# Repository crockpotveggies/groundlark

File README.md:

# Groundlark — open hardware for seismic and environmental monitoring

Groundlark is a family of hardware boards and companion software for seismic
and environmental monitoring. Each board has its own hardware directory, with
shared component libraries, interfaces and validation tools.

The family has **three products**: the Groundlark FPGA HAT, Skylark and
Burrowlark USB sensor heads. All share the sensor contracts, simulation tools and local workbench.

## Groundlark

**Seismic monitoring on a Raspberry Pi.** The active
[Groundlark FPGA HAT](hw/groundlark-fpga-hat/README.md), model **DAQHAT-01**, is a
140 × 56 mm, six-layer FR-4 board with three XYZ LSM6DSO IMUs and an ADS122C04
input for an external Racotech geophone, plus a fitted DLVR infrasound sensor and u-blox MAX-M10S GNSS with a side-facing SMA antenna connector. The stack is **Pi → HAT → Trenz
Artix-7 200T FPGA**. Pi acquisition works independently of a configured FPGA.

The [internal FPGA link](docs/fpga-host-link.md) provides six QSPI wires, UART,
reset and switched Pi-driven JTAG. An SPI echo bitstream is implemented;
accelerated sensor processing and native quad transfers remain future work.
The FPGA uses a separate Nexys Video-compatible 12 V, center-positive adapter through J83 and an onboard 3.326 V converter. See the [power limits](docs/trenz-hat.md).

**Status:** active prototype. Physical power, fit, timing, noise and thermal
qualification remain pending. See the [stack assembly guide](docs/stack-assembly.md),
[JLCPCB instructions](docs/jlcpcb-assembly.md) and [bench procedure](docs/bench-procedure.md).
The JLCPCB package targets one assembled HAT; sourcing, placement and J1 fit
checks remain open. Fabrication packages stay local in ignored `hw/releases/`.

*R3 [prototype enclosure](hw/mechanical/daqhat-01-case/README.md), current
140 mm HAT CAD with GNSS/SMA, infrasound, TI Pi supervision and independent FPGA power, vendor Trenz components and a detailed
[Pi 4B model](hw/shared/models/raspberrypi4/README.md) by integrated-circuit / FreeCAD
community (CC BY 3.0). Clear PETG appearance, risers, geophone and wiring are approximate.
Physical fit remains unqualified. [Render provenance](docs/images/groundlark-gnss.json).*

[Closed enclosure render provenance](docs/images/groundlark-gnss-closed.json).
Measured gain/offset workflows and PCB probe access are in the
[calibration guide](docs/calibration.md). Seismic recordings support local
[miniSEED export](docs/miniseed.md).

## Skylark

**Outdoor air-quality monitoring over USB.** [Skylark USB](hw/skylark-usb/README.md)
combines a vertical **90 × 100 mm PCB** with a removable sensor tray and a
**130 × 94 × 185 mm bell enclosure**.

- **Particles:** Plantower PMS5003, with separate downward-facing inlet and exhaust paths.
- **Gases:** socketed SGX-7SO2-AQ-20 sulfur dioxide and SGX-7H2S-AQ-25 hydrogen sulfide cells.
- **Weather:** SHT40 temperature/humidity and BMP390 barometric pressure.
- **Connection:** USB-C power and data through an STM32F072 microcontroller.
- **Housing:** printable bell, rear M4 keyhole mounts and a removable tray with
  separate PMS cradle and splash cover. Bottom ventilation is sheltered by a 25 mm skirt.

[Prototype firmware](sw/skylark/README.md) implements sensor acquisition and
USB streaming. The shared workbench includes Skylark simulation, recording/replay,
board-specific tests and an interactive 3D PCB. Gas data retains separate raw
working and auxiliary electrode counts; concentrations require calibration.

**Status:** Rev A PCB, Rev G enclosure and prototype firmware are implemented.
Physical fit, USB power behavior, analog performance, gas response and weather
resistance still require qualification. The ventilated enclosure has no assigned
IP rating. Follow the [PCB guide](hw/skylark-usb/README.md) and
[enclosure assembly instructions](hw/skylark-usb/mechanical/bell/README.md).

*Render: native PCB artwork and authored component models in the CAD-derived
tray, with the bell set beside it. Component bodies are dimension envelopes;
fasteners and cable dressing are illustrative. [Render provenance](docs/images/skylark-assembly.json).*

## Burrowlark

**Remote magnetic and enclosure-climate sensing over USB.**
[Burrowlark USB](hw/burrowlark-usb/README.md), model **DAQUSB-01**, carries an
RM3100 magnetometer and SHT45 temperature/humidity sensor. It connects to the Pi through USB-C for power and data.
The DLVR infrasound sensor is fitted on Groundlark DAQHAT-01.

**Status:** hardware design and workbench simulation are present; MCU firmware
and physical qualification remain pending. See the
[USB sensor-head guide](docs/usb-sensor-head.md) for interfaces and assembly details.

*Render: native 70 × 45 mm PCB with favicon, Burrowlark name and DAQUSB-01 / REV A2
silkscreen, RM3100 module and SHT45 U6/C10; the former infrasound
footprint and bypass capacitor are removed. Module, fuse and SHT45 bodies are simplified
dimensional envelopes. [Render provenance](hw/burrowlark-usb/boards/groundlark-field-head/render-provenance.json).*

## Sensor workbench

The dark-mode Python UI lets you switch between Groundlark, Skylark and
Burrowlark, with interactive 3D views, raw-data charts, stimulus/fault controls,
board-specific tests and recording/replay.
No hardware or Docker is required. Follow the
[beginner walkthrough](docs/sensor-workbench.md) to create your first signal.

```powershell
# Windows: set up once, then launch
./setup-ui.ps1 -Check
./ui.ps1
```

On Linux/macOS, use `sh ./setup-ui.sh --check`, then `sh ./ui.sh`.
Open **http://127.0.0.1:8080**. Tools and dependencies stay in ignored `.local/`.

This is an actual browser screenshot with simulated data. Select the geophone
can or its HAT input to highlight both and inspect the same ADC stream.
Use the **Board** selector for the FPGA HAT, Burrowlark or Skylark.
**Test selected board** runs the selected board’s checks; the HAT test covers all
six sensors over eight simulated seconds. IMU, ADC and GNSS use production Pi
drivers on modeled buses; infrasound uses a raw-response model pending its Pi
driver. Signal checks and recordings/results are downloadable.
The Groundlark GNSS panel also models disconnected or shorted antennas, lock
loss and recovery, and PPS loss independently.
The UI simulates and replays; physical acquisition uses the [Pi software](docs/sensor-software.md).
Live seismic capture stores raw geophone and IMU counts locally as
[miniSEED 3](docs/miniseed.md), with SSREC companions for diagnostics and replay.

## Project files and tests

| Directory | Contents |
| --- | --- |
| [hw/](hw/README.md) | Four product directories, shared component resources, hardware checks and SPICE. |
| [sw/](sw/README.md) | Pi acquisition, contracts, simulator, FPGA and remote firmware interfaces. |
| [docs/](docs/README.md) | Setup, hardware specifications, assembly, interfaces and testing instructions. |
| [environment/](docs/portable-lab.md) | Pinned Docker test environment and bounded cleanup tooling. |

For the full test environment, run `./lab.ps1 build` once, then `./lab.ps1 test`.
Use `./lab.ps1 test -Profile software` for sensor contracts, acquisition,
recording/replay and recovery. See the [portable lab guide](docs/portable-lab.md)
for Linux commands, test scope, five-run retention and cleanup.

Hardware sources: [DAQHAT-01 circuit](hw/groundlark-fpga-hat/elec/hat_trenz.ato),
[KiCad PCB](hw/groundlark-fpga-hat/boards/groundlark-daqhat-01/groundlark-daqhat-01.kicad_pcb),
[Burrowlark DAQUSB-01](hw/burrowlark-usb/boards/groundlark-field-head/groundlark-field-head.kicad_pcb), and
[Skylark USB](hw/skylark-usb/boards/skylark-usb/skylark-usb.kicad_pcb).
See [build instructions](docs/build.md) and [source references](docs/sources.md).

## License

Project-authored code, hardware designs and documentation use the [MIT License](LICENSE).
Third-party assets and dependencies retain their own licenses and attribution.

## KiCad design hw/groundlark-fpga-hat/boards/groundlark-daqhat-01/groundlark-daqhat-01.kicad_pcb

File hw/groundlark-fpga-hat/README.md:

# Groundlark FPGA HAT — DAQHAT-01

Underside TP90–TP93 provide passive calibration probe access; see the [bench calibration guide](../../docs/calibration.md). No additional GPIO or enclosure opening is required.

The active 140 × 56 mm, six-layer Trenz carrier combines three XYZ IMUs and
an ADS122C04 input for an external Racotech geophone, plus a fitted DLVR-F50D
infrasound pressure sensor on I2C1 (0x28). The stack is Raspberry Pi,
DAQHAT-01, then Trenz TE0712-03-81I36-A. Physical qualification remains pending.
J90 uses a horizontal Phoenix 1803280 header with the existing 1803581 cable
plug. Pin order remains positive, negative, shield.

MAX-M10S GNSS uses Pi I²C1 and BCM24 PPS, with a side-facing SMA and a
TPS2553 antenna fault limiter. ISO1640 side 2 faces the Pi/GNSS bus. J130 feeds
the separate MSPM0L1106 supervisor and 5.115 V Pi supply; battery policy and
MCU firmware remain pending. See [GNSS setup](../../docs/gnss-hardware.md).

J83 takes a Nexys Video-compatible 12 V, center-positive 5.5/2.1 mm adapter
rated at least 3 A. It faces the opposite edge from the geophone. U80 supplies
the FPGA independently of the Pi, with a 3 A output allocation; SW80 turns this
supply off/on. The first 25 mm of the extension contains FPGA input protection and conversion. Check the documented voltage, thermal and enclosure limits before
building; the supply remains an unqualified prototype.

- [Electrical source](elec/hat_trenz.ato)
- [Placement inputs](layout/placement.json)
- [Routed KiCad project](boards/groundlark-daqhat-01/groundlark-daqhat-01.kicad_pro)
- [Native routing snapshot](boards/groundlark-daqhat-01/groundlark-daqhat-01.ses)
- [Hardware and power specifications](../../docs/trenz-hat.md)
- [Pi and external source budgets](../../docs/power-supplies.md)
- [Sensor bandwidth and timing](../../docs/sensor-response.md)
- [Assembly instructions](../../docs/stack-assembly.md)

Build target: `trenz_hat` in [hw/ato.yaml](../ato.yaml). Use the root portable lab
for validation. `simulation/` contains bounded supporting-circuit models;
`mechanical/` retains earlier mechanical artifacts with their recorded status.
FPGA sources remain under [sw/fpga/](../../sw/fpga/README.md).

Assembly uses an 8.5 mm JLCPCB socket, two external GPIO risers and measured
supports (28.06 mm nominal Pi gap). Sensor supply and bias returns have local
ground stitches. Procurement accepts in-stock PCB selections with component
MOQ 1; see [JLCPCB assembly](../../docs/jlcpcb-assembly.md).

Use the [R3 enclosure](../mechanical/daqhat-01-case/README.md) for the 140 × 56 mm
board. It adds power-wing supports, a rear DC opening opposite the geophone and
switch access. First-print fit and thermal qualification remain pending.

## Pi power supervisor

J130 accepts **8–18 V DC** from an externally protected battery/controller.
U130 is TI MSPM0L1105TRHBR; U131 powers it continuously while U132/U133 supply
and disconnect the Pi through header pins 2/4. The combined Pi/HAT allocation
is 3 A at nominal 5.149 V, for the Pi 4 stack. Do not simultaneously power the
Pi through USB-C. Keep J83's separate 12 V FPGA input independent.

Battery thresholds and delays are configurable placeholders, shipped disabled
in [power-policy.example.json](../../sw/pi/deploy/power-policy.example.json).
Target MCU firmware and physical power qualification remain pending. An
unprogrammed MCU leaves the Pi off; fitting the JP130 shunt provides manual
bench operation. Remove it before automatic supervision. See the
[operating specification](../../docs/power-supplies.md#pi-supervisor-and-battery-input).

## GNSS timing

U21 is a MAX-M10S-00B on Pi I2C1 (0x42); BCM24/header 18 captures PPS.
J140 is a side-facing SMA for a 3.3 V active antenna drawing at most 20 mA.
The 140 x 56 mm outline and independent FPGA power remain unchanged. Use the
updated R3 enclosure with its +X antenna access slot. See [antenna setup](../../docs/gnss-hardware.md)
and [timing capture/correlation](../../docs/utc-timing.md). Browser tests cover
modeled lock/PPS loss and recording/replay; physical millisecond alignment remains unqualified.

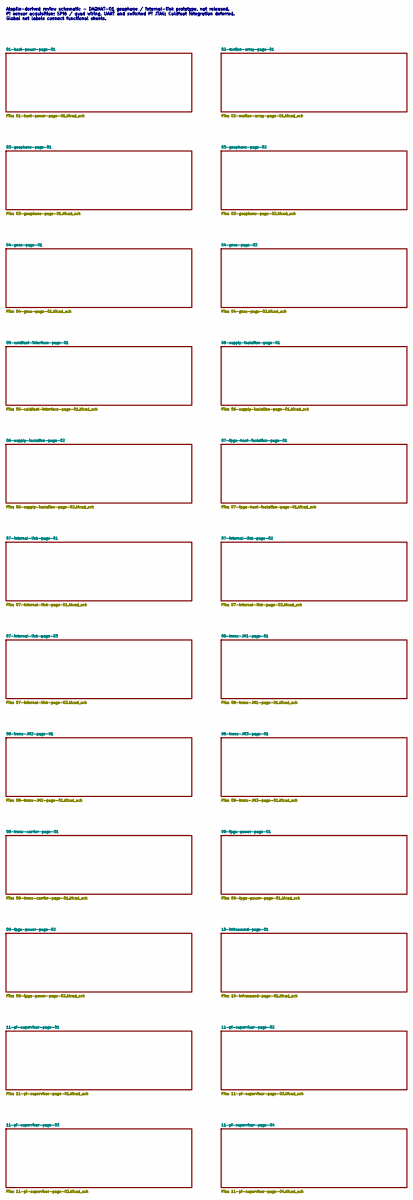
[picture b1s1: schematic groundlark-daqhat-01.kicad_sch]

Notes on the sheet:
Atopile-derived review schematic - DAQHAT-01 geophone / internal-link prototype, not released. Pi sensor acquisition; SPI6 / quad wiring, UART and switched Pi JTAG; Coldfoot integration deferred. Global net labels connect functional sheets.

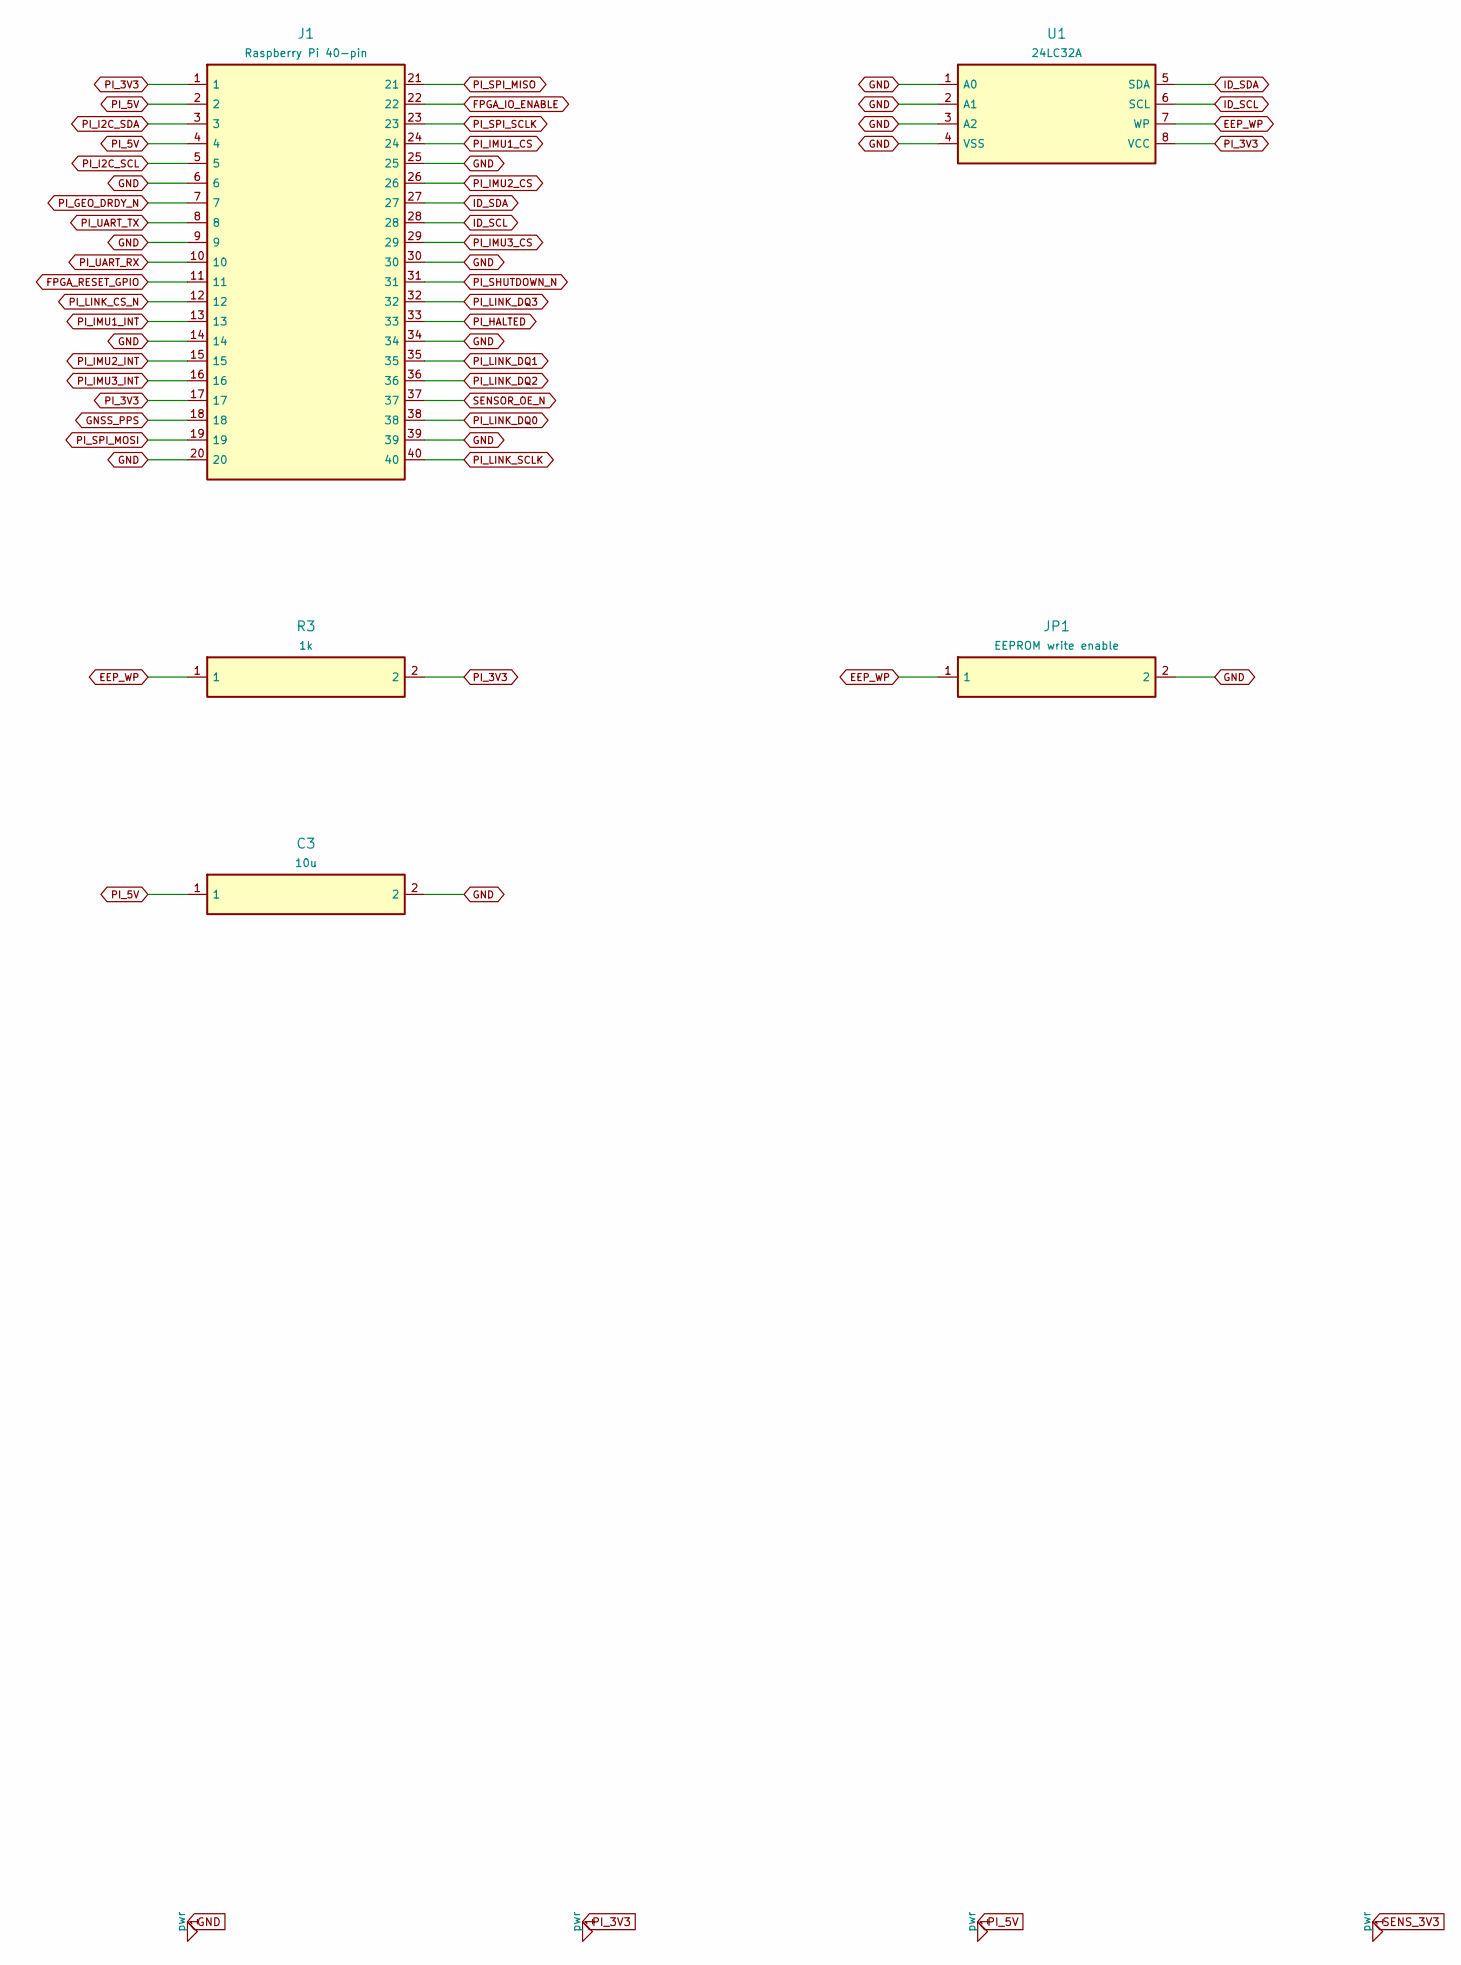
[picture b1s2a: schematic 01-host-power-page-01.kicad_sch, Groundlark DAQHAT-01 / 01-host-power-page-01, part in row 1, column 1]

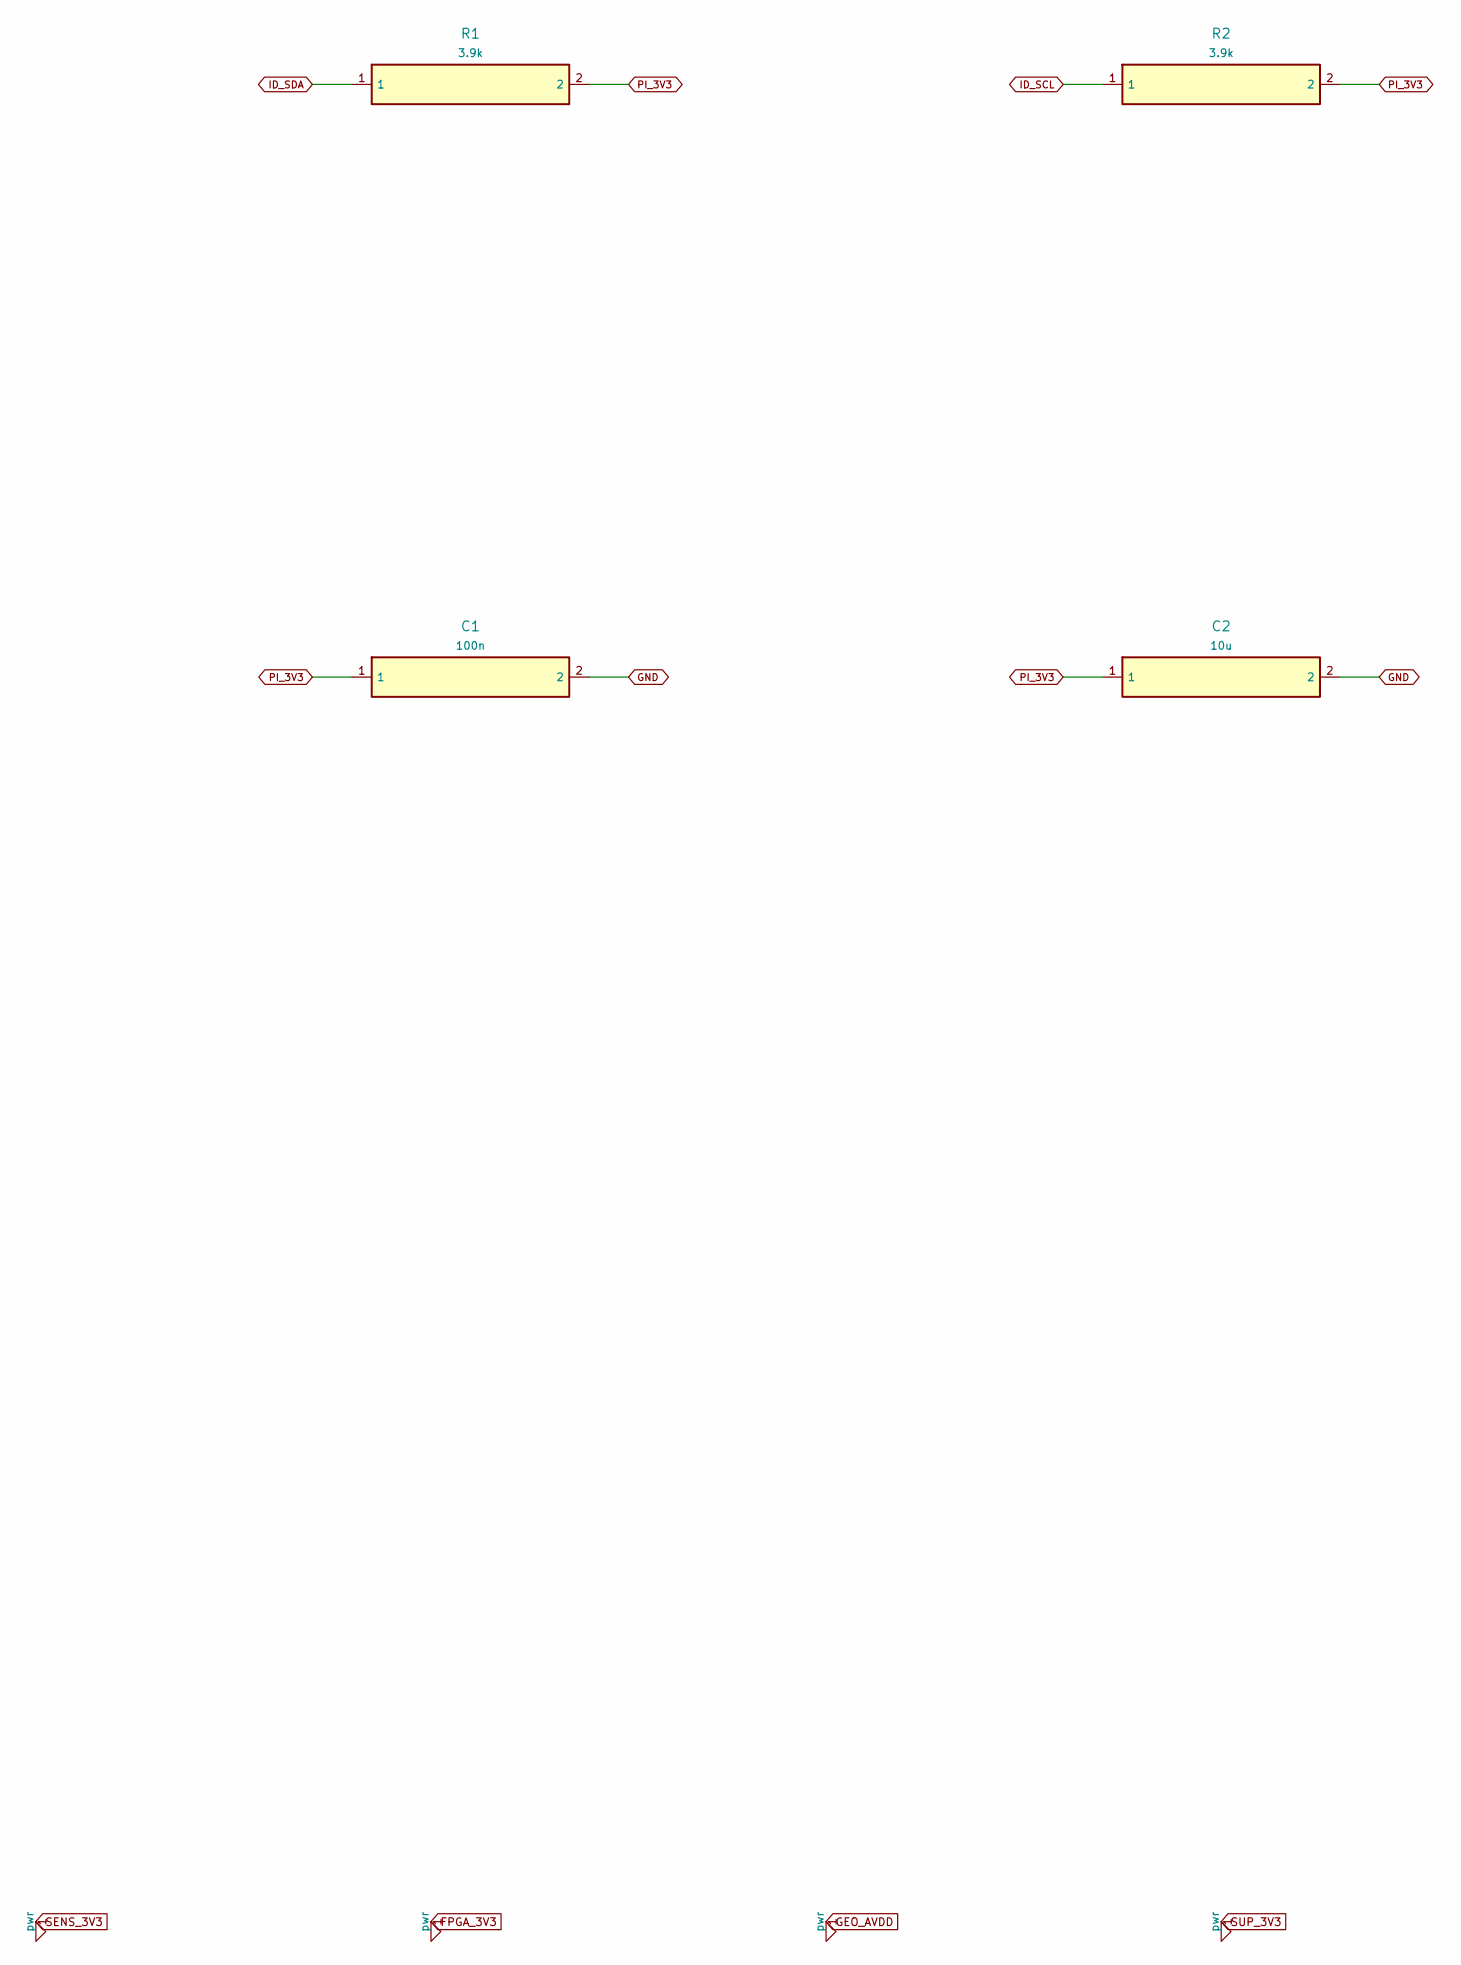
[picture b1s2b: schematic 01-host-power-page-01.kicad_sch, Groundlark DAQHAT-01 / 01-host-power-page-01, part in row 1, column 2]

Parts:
C1: 100n; Capacitor_SMD__C_0603_1608Metric; MPN GRM188R71H104KA93D
C2, C3: 10u; Capacitor_SMD__C_0805_2012Metric; MPN GRM21BR61A106KE19L
J1: Raspberry Pi 40-pin; Connector_PinHeader_2.54mm__PinHeader_2x20_P2.54mm_Vertical; MPN Samtec ESQ-120-23-G-D
JP1: EEPROM write enable; Connector_PinHeader_2.54mm__PinHeader_1x02_P2.54mm_Vertical; MPN EEPROM write enable
R1, R2: 3.9k; Resistor_SMD__R_0603_1608Metric; MPN RC0603FR-073K9L
R3: 1k; Resistor_SMD__R_0603_1608Metric; MPN RC0603FR-071KL
U1: 24LC32A; Package_SO__SOIC-8_3.9x4.9mm_P1.27mm; MPN 24LC32A-I/SN

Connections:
EEP_WP: JP1.1, R3.1, U1.7 (WP)
FPGA_IO_ENABLE: J1.22; also elsewhere on the board
FPGA_RESET_GPIO: J1.11; also elsewhere on the board
GND: C1.2, C2.2, C3.2, J1.6, J1.9, J1.14, J1.20, J1.25, J1.30, J1.34, J1.39, JP1.2, U1.1 (A0), U1.2 (A1), U1.3 (A2), U1.4 (VSS); also elsewhere on the board
GNSS_PPS: J1.18; also elsewhere on the board
ID_SCL: J1.28, R2.1, U1.6 (SCL)
ID_SDA: J1.27, R1.1, U1.5 (SDA)
PI_3V3: C1.1, C2.1, J1.1, J1.17, R1.2, R2.2, R3.2, U1.8 (VCC); also elsewhere on the board
PI_5V: C3.1, J1.2, J1.4; also elsewhere on the board
PI_GEO_DRDY_N: J1.7; also elsewhere on the board
PI_HALTED: J1.33; also elsewhere on the board
PI_I2C_SCL: J1.5; also elsewhere on the board
PI_I2C_SDA: J1.3; also elsewhere on the board
PI_IMU1_CS: J1.24; also elsewhere on the board
PI_IMU1_INT: J1.13; also elsewhere on the board
PI_IMU2_CS: J1.26; also elsewhere on the board
PI_IMU2_INT: J1.15; also elsewhere on the board
PI_IMU3_CS: J1.29; also elsewhere on the board
PI_IMU3_INT: J1.16; also elsewhere on the board
PI_LINK_CS_N: J1.12; also elsewhere on the board
PI_LINK_DQ0: J1.38; also elsewhere on the board
PI_LINK_DQ1: J1.35; also elsewhere on the board
PI_LINK_DQ2: J1.36; also elsewhere on the board
PI_LINK_DQ3: J1.32; also elsewhere on the board
PI_LINK_SCLK: J1.40; also elsewhere on the board
PI_SHUTDOWN_N: J1.31; also elsewhere on the board
PI_SPI_MISO: J1.21; also elsewhere on the board
PI_SPI_MOSI: J1.19; also elsewhere on the board
PI_SPI_SCLK: J1.23; also elsewhere on the board
PI_UART_RX: J1.10; also elsewhere on the board
PI_UART_TX: J1.8; also elsewhere on the board
SENSOR_OE_N: J1.37; also elsewhere on the board

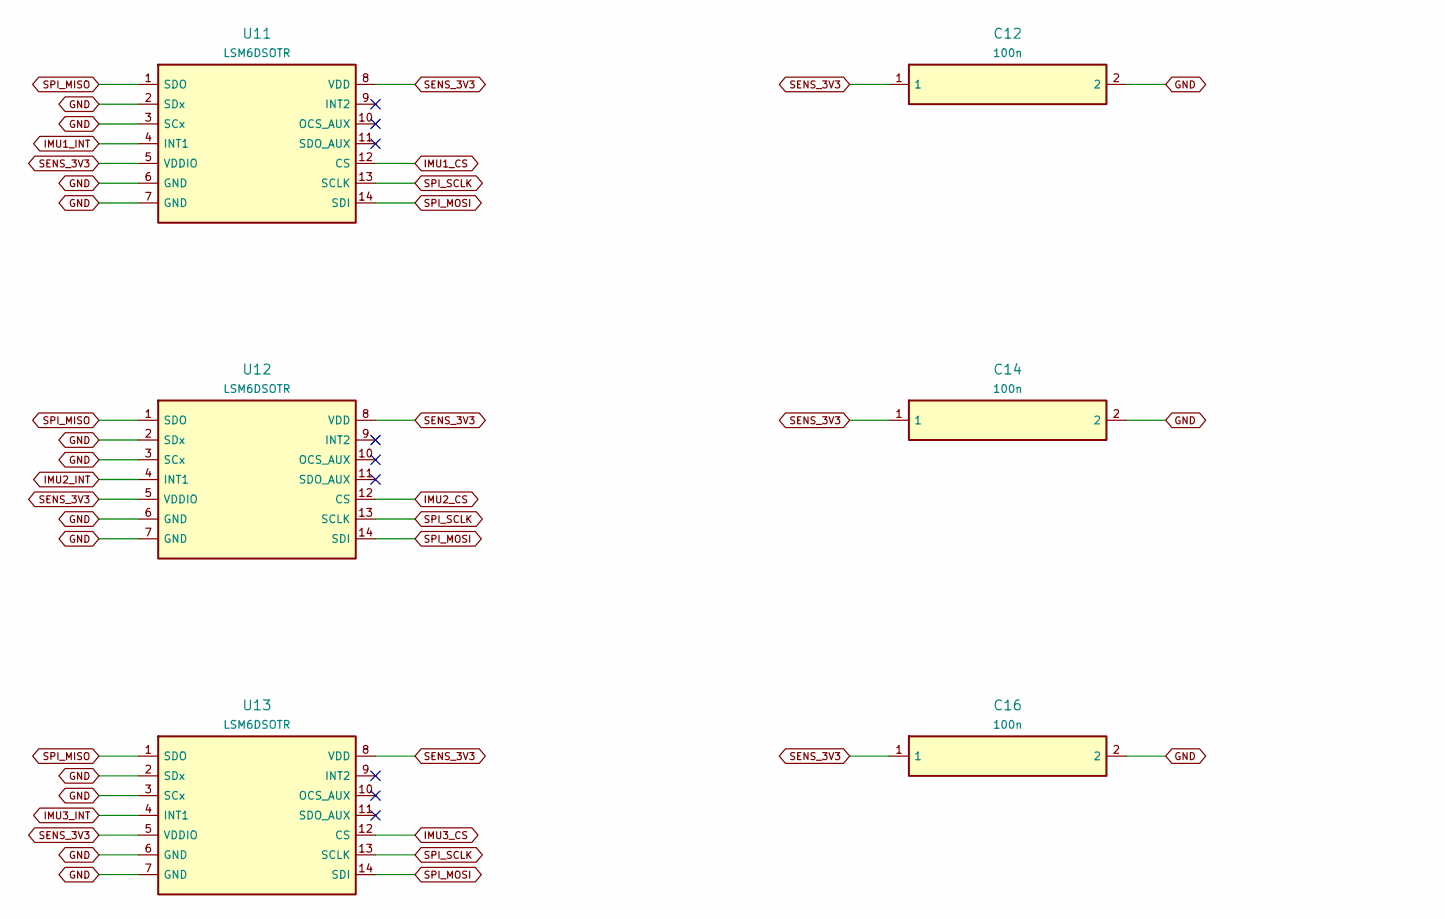
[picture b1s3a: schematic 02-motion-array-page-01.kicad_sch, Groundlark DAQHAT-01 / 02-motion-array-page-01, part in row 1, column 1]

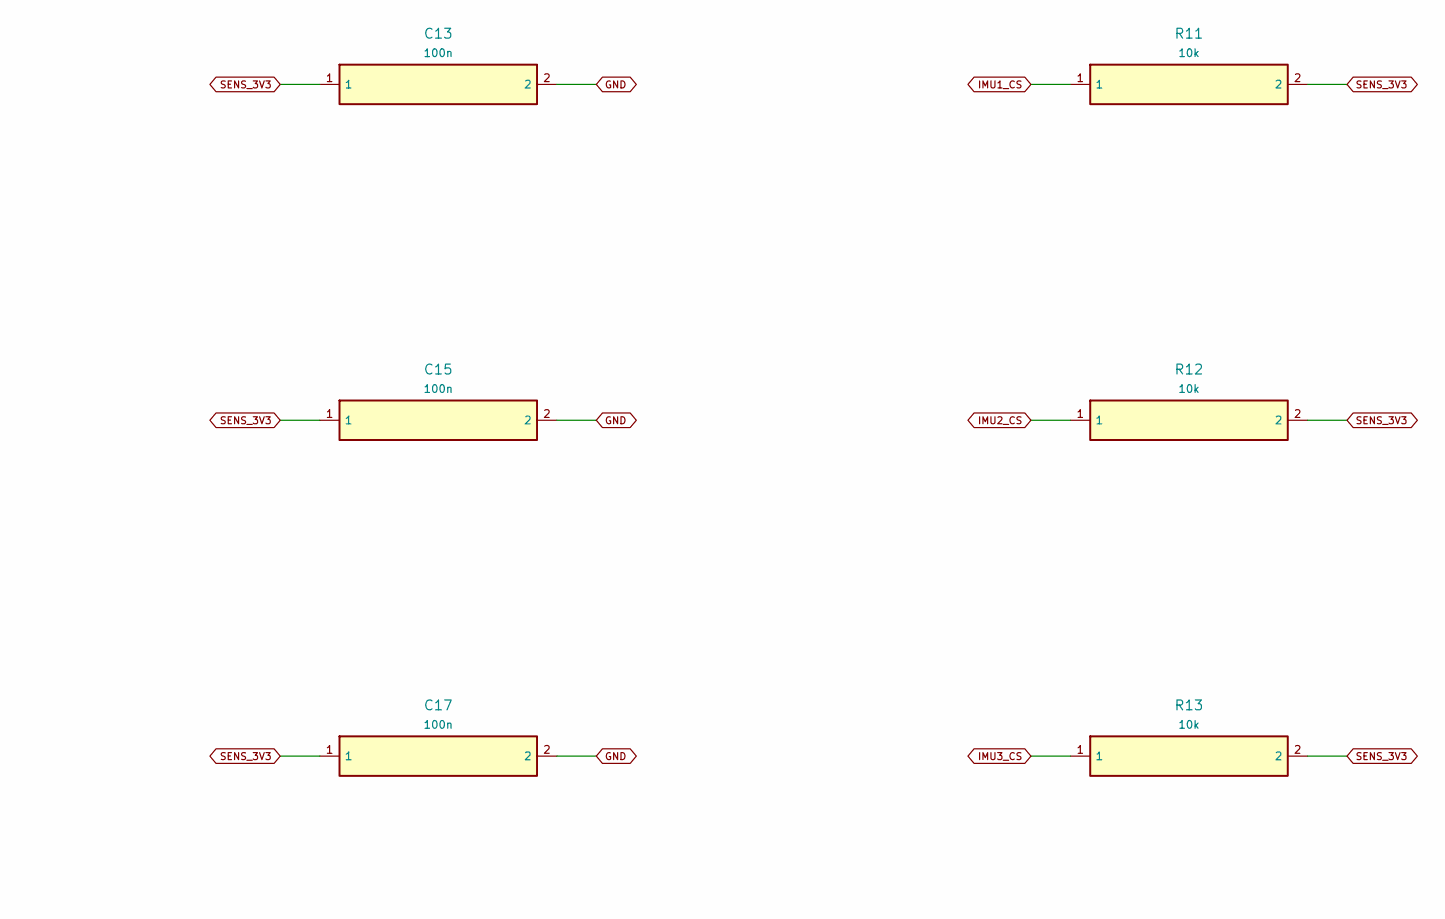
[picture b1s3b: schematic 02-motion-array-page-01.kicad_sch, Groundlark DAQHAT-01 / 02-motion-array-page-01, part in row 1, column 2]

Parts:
C12, C13, C14, C15, C16, C17: 100n; Capacitor_SMD__C_0402_1005Metric; MPN GRM155R71C104KA88D
R11, R12, R13: 10k; Resistor_SMD__R_0603_1608Metric; MPN RC0603FR-0710KL
U11, U12, U13: LSM6DSOTR; Package_LGA__LGA-14_3x2.5mm_P0.5mm_LayoutBorder3x4y; MPN LSM6DSOTR

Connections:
GND: C12.2, C13.2, C14.2, C15.2, C16.2, C17.2, U11.2 (SDx), U11.3 (SCx), U11.6 (GND), U11.7 (GND), U12.2 (SDx), U12.3 (SCx), U12.6 (GND), U12.7 (GND), U13.2 (SDx), U13.3 (SCx), U13.6 (GND), U13.7 (GND); also elsewhere on the board
IMU1_CS: R11.1, U11.12 (CS); also elsewhere on the board
IMU1_INT: U11.4 (INT1); also elsewhere on the board
IMU2_CS: R12.1, U12.12 (CS); also elsewhere on the board
IMU2_INT: U12.4 (INT1); also elsewhere on the board
IMU3_CS: R13.1, U13.12 (CS); also elsewhere on the board
IMU3_INT: U13.4 (INT1); also elsewhere on the board
SENS_3V3: C12.1, C13.1, C14.1, C15.1, C16.1, C17.1, R11.2, R12.2, R13.2, U11.5 (VDDIO), U11.8 (VDD), U12.5 (VDDIO), U12.8 (VDD), U13.5 (VDDIO), U13.8 (VDD); also elsewhere on the board
SPI_MISO: U11.1 (SDO), U12.1 (SDO), U13.1 (SDO); also elsewhere on the board
SPI_MOSI: U11.14 (SDI), U12.14 (SDI), U13.14 (SDI); also elsewhere on the board
SPI_SCLK: U11.13 (SCLK), U12.13 (SCLK), U13.13 (SCLK); also elsewhere on the board
u11-9: U11.9 (INT2)
u11-10: U11.10 (OCS_AUX)
u11-11: U11.11 (SDO_AUX)
u12-9: U12.9 (INT2)
u12-10: U12.10 (OCS_AUX)
u12-11: U12.11 (SDO_AUX)
u13-9: U13.9 (INT2)
u13-10: U13.10 (OCS_AUX)
u13-11: U13.11 (SDO_AUX)

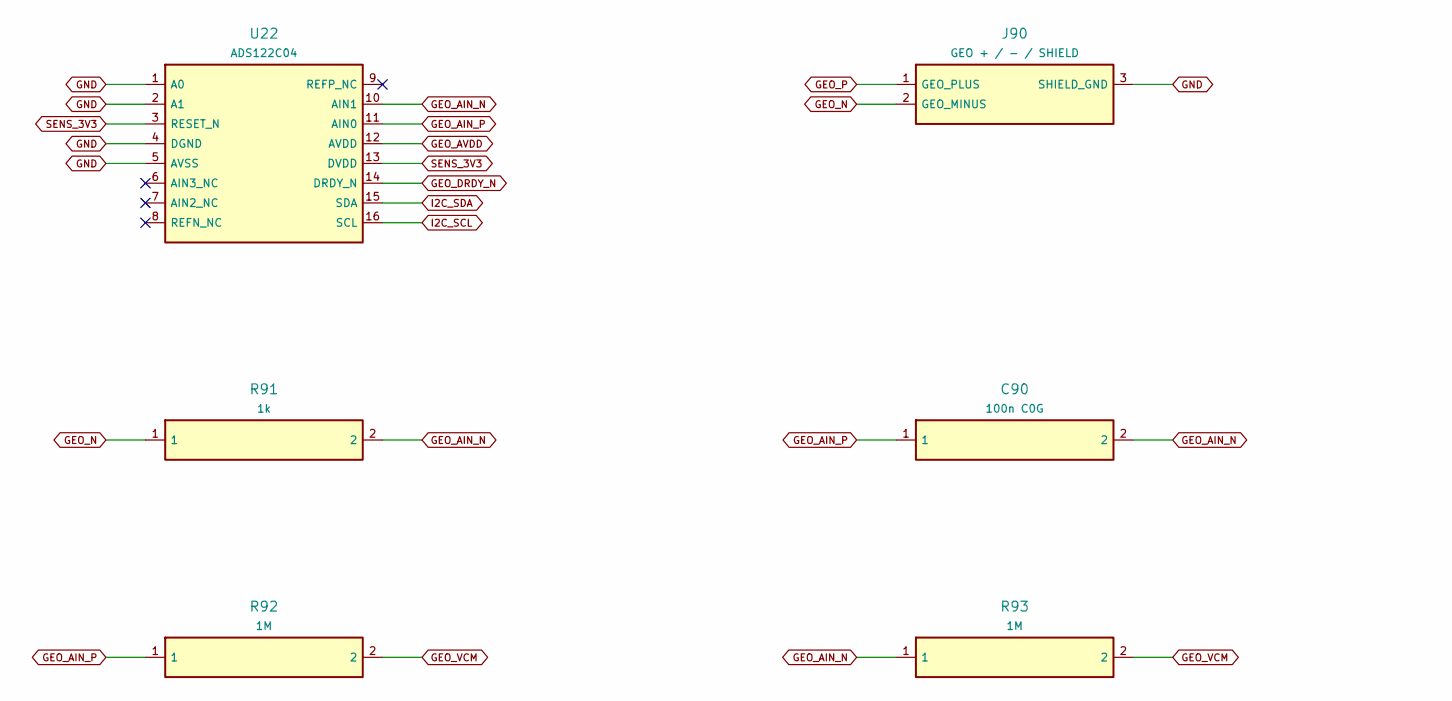
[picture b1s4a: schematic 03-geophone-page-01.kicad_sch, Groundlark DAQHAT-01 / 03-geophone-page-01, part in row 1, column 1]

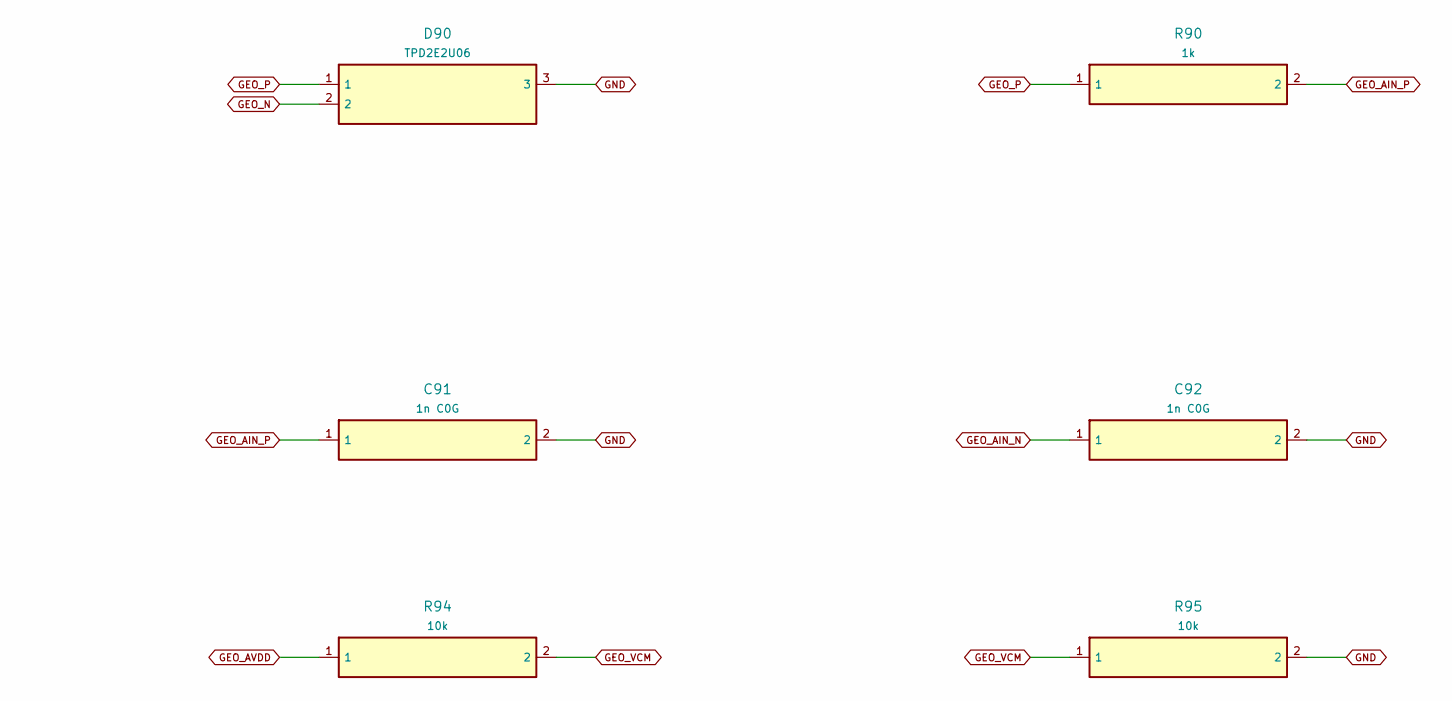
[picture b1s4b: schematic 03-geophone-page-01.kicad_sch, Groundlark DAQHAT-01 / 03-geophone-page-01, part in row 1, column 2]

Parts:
C90: 100n C0G; Capacitor_SMD__C_1206_3216Metric; MPN C3216C0G1H104J160AA
C91, C92: 1n C0G; Capacitor_SMD__C_0603_1608Metric; MPN C0603C102J5GACTU
D90: TPD2E2U06; Package_TO_SOT_SMD__SOT-323_SC-70; MPN TPD2E2U06DCKR
J90: GEO + / - / SHIELD; Connector_Phoenix_MC__PhoenixContact_MC_1,5_3-G-3.81_1x03_P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; MPN 1803280
R90, R91: 1k; Resistor_SMD__R_0603_1608Metric; MPN RC0603FR-071KL
R92, R93: 1M; Resistor_SMD__R_0603_1608Metric; MPN RC0603FR-071ML
R94, R95: 10k; Resistor_SMD__R_0603_1608Metric; MPN RC0603FR-0710KL
U22: ADS122C04; Package_SO__TSSOP-16_4.4x5mm_P0.65mm; MPN ADS122C04IPWR

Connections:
GEO_AIN_N: C90.2, C92.1, R91.2, R93.1, U22.10 (AIN1)
GEO_AIN_P: C90.1, C91.1, R90.2, R92.1, U22.11 (AIN0)
GEO_AVDD: R94.1, U22.12 (AVDD); also elsewhere on the board
GEO_DRDY_N: U22.14 (DRDY_N); also elsewhere on the board
GEO_N: D90.2, J90.2 (GEO_MINUS), R91.1
GEO_P: D90.1, J90.1 (GEO_PLUS), R90.1
GEO_VCM: R92.2, R93.2, R94.2, R95.1; also elsewhere on the board
GND: C91.2, C92.2, D90.3, J90.3 (SHIELD_GND), R95.2, U22.1 (A0), U22.2 (A1), U22.4 (DGND), U22.5 (AVSS); also elsewhere on the board
I2C_SCL: U22.16 (SCL); also elsewhere on the board
I2C_SDA: U22.15 (SDA); also elsewhere on the board
SENS_3V3: U22.3 (RESET_N), U22.13 (DVDD); also elsewhere on the board
u22-6: U22.6 (AIN3_NC)
u22-7: U22.7 (AIN2_NC)
u22-8: U22.8 (REFN_NC)
u22-9: U22.9 (REFP_NC)

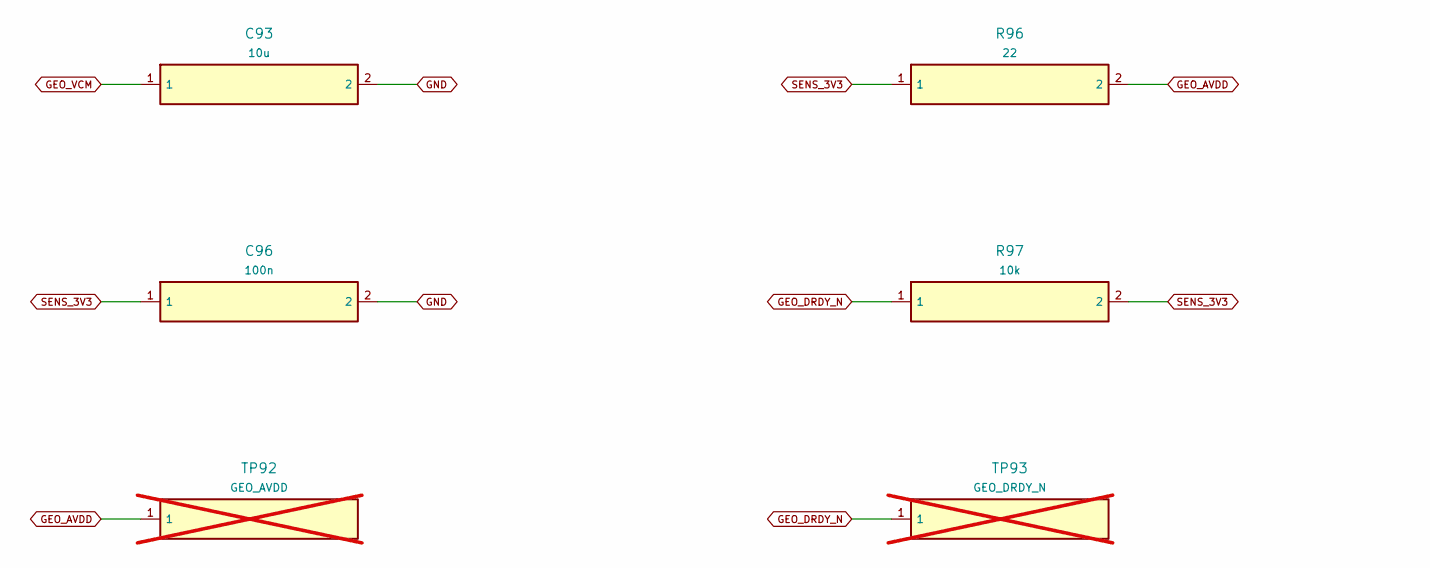
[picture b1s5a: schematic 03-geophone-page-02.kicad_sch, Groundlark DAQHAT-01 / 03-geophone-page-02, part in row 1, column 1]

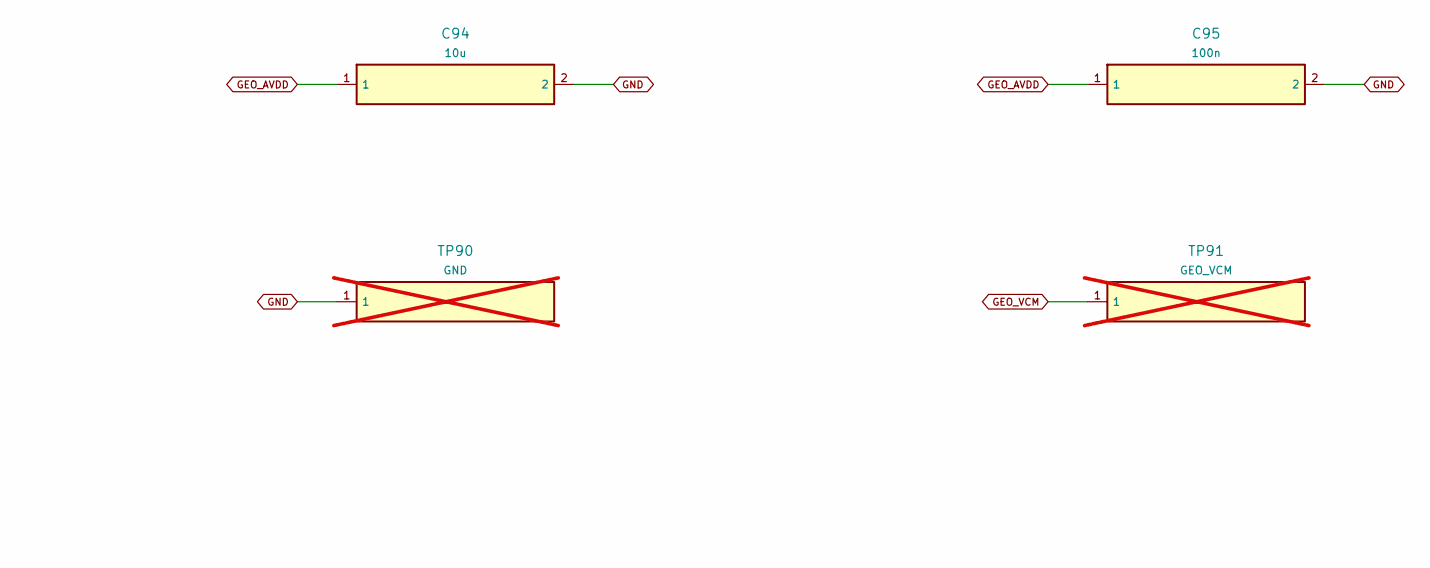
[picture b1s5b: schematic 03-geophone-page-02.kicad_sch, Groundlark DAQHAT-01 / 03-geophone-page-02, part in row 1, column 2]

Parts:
C93, C94: 10u; Capacitor_SMD__C_0805_2012Metric; MPN GRM21BR61A106KE19L
C95, C96: 100n; Capacitor_SMD__C_0603_1608Metric; MPN GRM188R71H104KA93D
R96: 22; Resistor_SMD__R_0603_1608Metric; MPN RC0603FR-0722RL
R97: 10k; Resistor_SMD__R_0603_1608Metric; MPN RC0603FR-0710KL
TP90: GND; TestPoint__TestPoint_Pad_D1.5mm; MPN PCB copper; not fitted
TP91: GEO_VCM; TestPoint__TestPoint_Pad_D1.5mm; MPN PCB copper; not fitted
TP92: GEO_AVDD; TestPoint__TestPoint_Pad_D1.5mm; MPN PCB copper; not fitted
TP93: GEO_DRDY_N; TestPoint__TestPoint_Pad_D1.5mm; MPN PCB copper; not fitted

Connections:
GEO_AVDD: C94.1, C95.1, R96.2, TP92.1; also elsewhere on the board
GEO_DRDY_N: R97.1, TP93.1; also elsewhere on the board
GEO_VCM: C93.1, TP91.1; also elsewhere on the board
GND: C93.2, C94.2, C95.2, C96.2, TP90.1; also elsewhere on the board
SENS_3V3: C96.1, R96.1, R97.2; also elsewhere on the board
